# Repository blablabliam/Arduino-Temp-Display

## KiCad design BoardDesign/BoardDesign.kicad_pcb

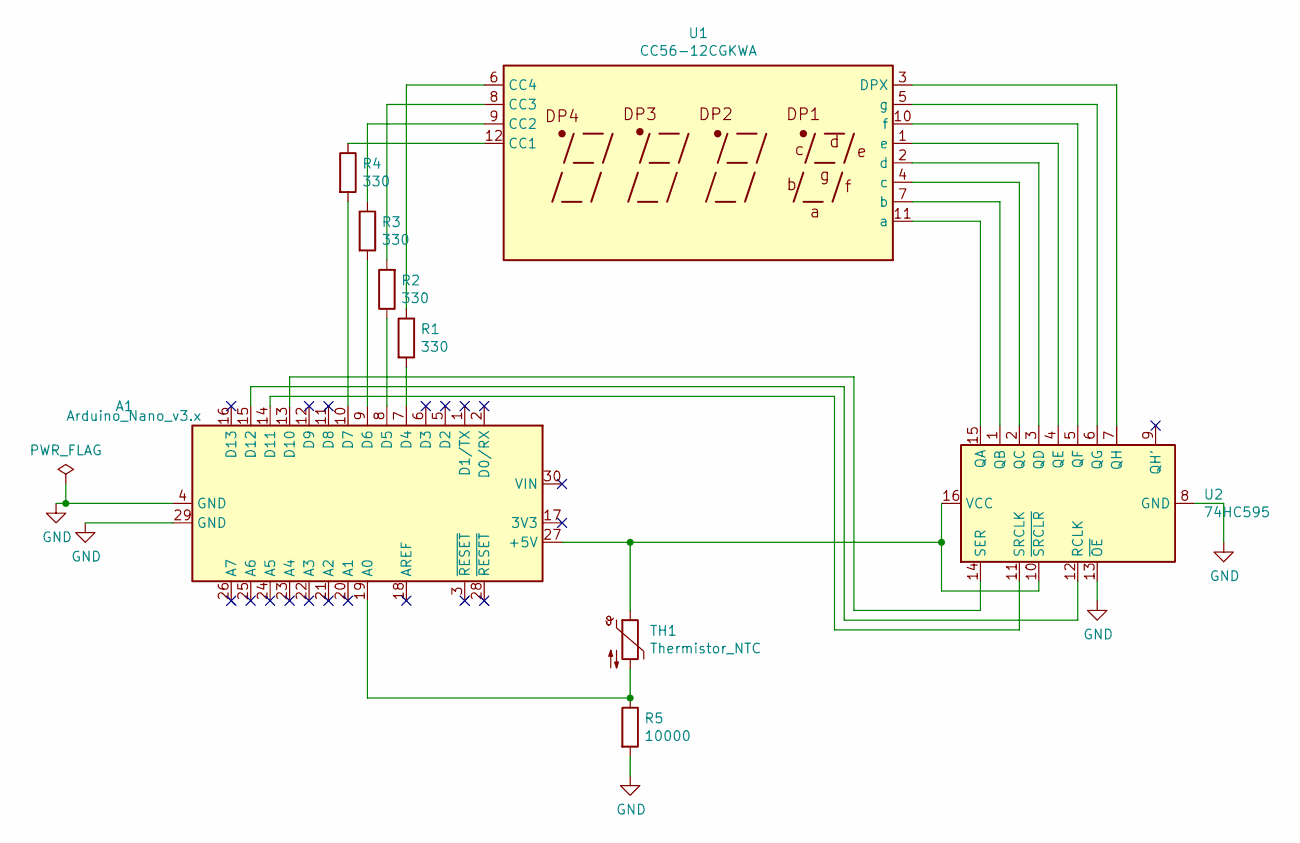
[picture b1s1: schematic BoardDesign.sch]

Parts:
A1: Arduino_Nano_v3.x; Arduino_Nano_WithMountingHoles
R1, R2, R3, R4: 330; R_0805_2012Metric
R5: 10000; R_0805_2012Metric
TH1: Thermistor_NTC; R_0805_2012Metric
U1: CC56-12CGKWA; HKL-8041-AB
U2: 74HC595; DIP-16_W7.62mm_LongPads

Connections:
GND: A1.4 (GND), A1.29 (GND), R5.2, U2.8 (GND), U2.13 (~OE)
unnamed: A1.7 (D4), R1.2
unnamed: A1.8 (D5), R2.1
unnamed: A1.9 (D6), R3.2
unnamed: A1.10 (D7), R4.2
unnamed: A1.13 (D10), U2.14 (SER)
unnamed: A1.14 (D11), U2.11 (SRCLK)
unnamed: A1.15 (D12), U2.12 (RCLK)
unnamed: A1.19 (A0), R5.1, TH1.2
unnamed: A1.27 (+5V), TH1.1, U2.10 (~SRCLR), U2.16 (VCC)
unnamed: R1.1, U1.6 (CC4)
unnamed: R2.2, U1.8 (CC3)
unnamed: R3.1, U1.9 (CC2)
unnamed: R4.1, U1.12 (CC1)
unnamed: U1.1 (e), U2.4 (QE)
unnamed: U1.2 (d), U2.3 (QD)
unnamed: U1.3 (DPX), U2.7 (QH)
unnamed: U1.4 (c), U2.2 (QC)
unnamed: U1.5 (g), U2.6 (QG)
unnamed: U1.7 (b), U2.1 (QB)
unnamed: U1.10 (f), U2.5 (QF)
unnamed: U1.11 (a), U2.15 (QA)

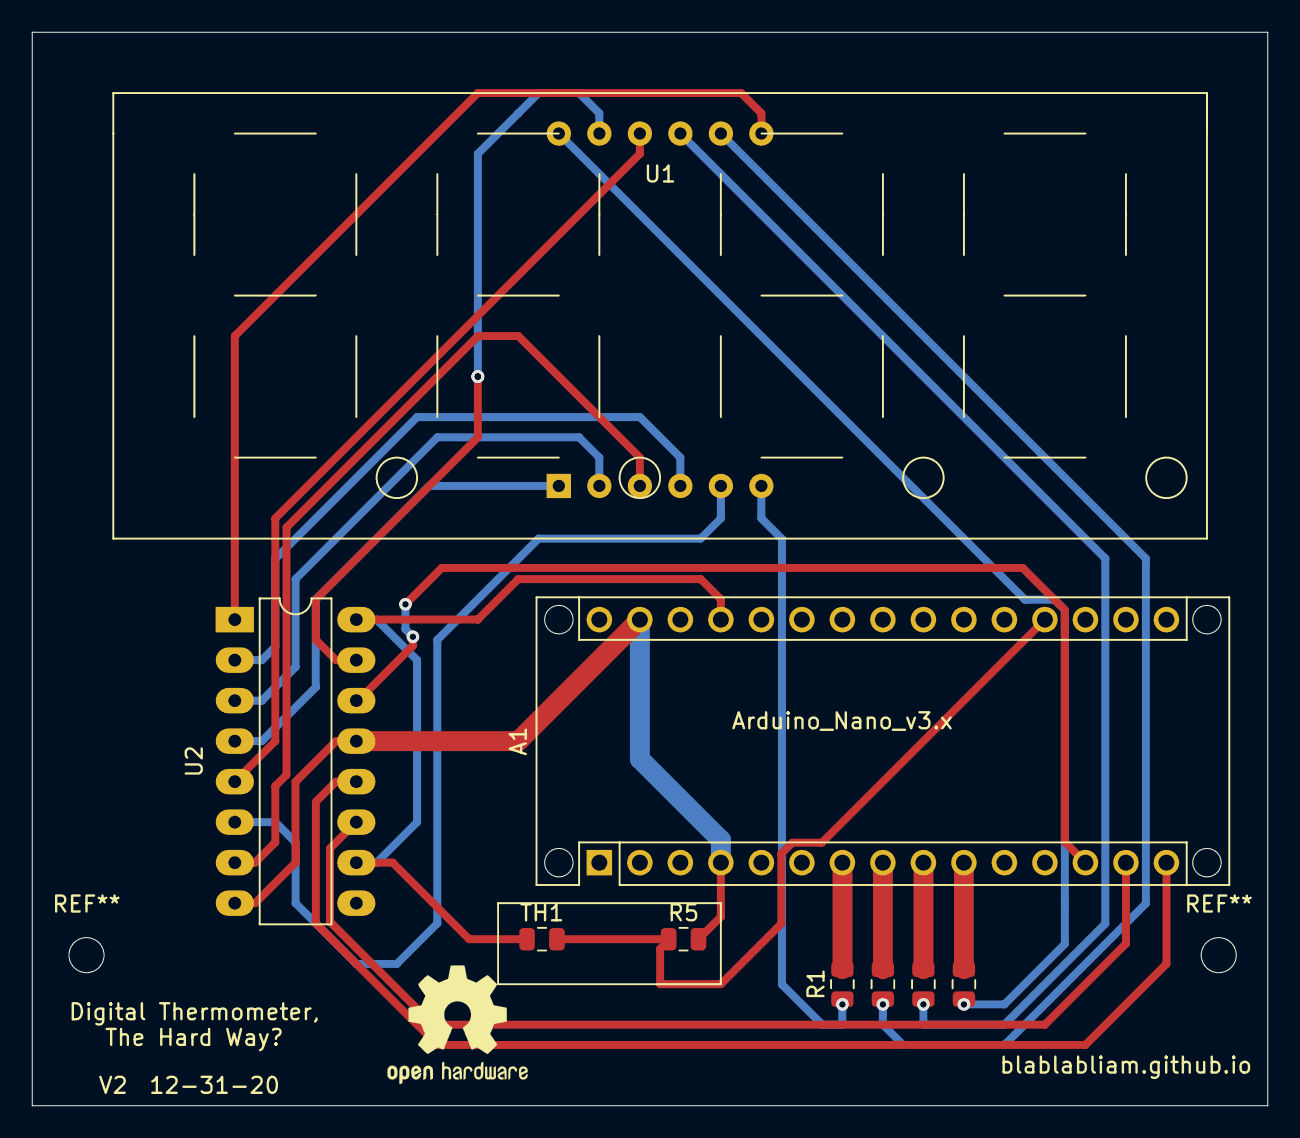
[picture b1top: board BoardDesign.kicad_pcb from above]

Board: 2 copper layers, 77.5 x 67.3 mm, 9 parts (0 on the bottom side), 22 nets.

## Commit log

2020-11-29 :confetti_ball: Added .gitattributes & .gitignore files
2020-11-29 Started Project
    Added arduino uno code and started the board design process.
2020-11-29 Finished an UNO schematic in KiCad
2020-12-02 Fixed the board design to implement proper GND tags.
2020-12-02 Finished the layout for the first board.
    Added files needed to have a board fabricated.
2020-12-03 Fixed Issue with R4 Trace
    Had an accidental junction in the schematic.
2020-12-19 Fixed issue with 330 R trace on wrong side of board
    The 330 ohm resistors have the traces on the wrong side of the board, so
    that the resistors are not actually connected to anything. Fixed with 4
    vias.
2021-01-01 Finished the V2 Design
    Corrected the general issues with the board. Notably, fixed the
    disconnected traces to the 330 Ohm resistors, swapped the positions of
    the thermistor and loading resistor, added M2 screw holes and moved pin
    13 to pin 10 for the coms to the shift register.
2021-01-01 Updated code to reflect Nano board
    Added picture for social media, as well.
2021-01-01 Updated the manufacture files
    Also moved the code to an Arduino folder to make it easy to find.
